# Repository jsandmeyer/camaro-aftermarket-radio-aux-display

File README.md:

## Camaro Temperature & Reverse Sensor Display Shim

This provides resources to help you build something to get the temperature display of a PAC RPK5-GM4102 (or 4101) to function while using a Maestro RR instead of the box that came with the PAC kit.
This is useful if you want to have the Maestro functions to get/update vehicle data, but have the nice function and appearance of the OEM-style HVAC knobs provided by the PAC kit.

### Important
This project is not endorsed by GM, the makers of any trim kits (PAC, iDatalink) or my aftermarket radio, any forum or their users, or anyone else, including any entities named in this repository.
It is a personal project which I have completed, and I have taken a substantial risk to my own property by building and installing this project.

This project (except for PCB footprints supplied by KiCad's included files) is licensed under the MIT license.
Please read the attached LICENSE document.
All code was written by myself, based on documentation provided by libraries or electronic part providers.
All PCB design (except for some footprints) was completed by myself.

### Background

[This forum post on camaro5.com](https://www.camaro5.com/forums/showthread.php?t=588249) goes over the process of combining the two dash kit elements.
Note the OP and others never got the temperature display to work.
This is because the PAC trim component's harness does not have CANBUS access, and the PAC controller was relaying the temperature (and possibly other data) over the Serial line running between the radio and HVAC harnesses.

### Goal

My goal was simply to display the temperature on the OLED.
In the process of design, I also decied to have it show backup sensor data.
The original MyLink radio showed a triangle with an exclamation point in one of five positions over the backup camera when reversing, and it would change color and flash depending on distance.
I wanted to display something similar on the OLED when reversing, because no aftermarket radios seem to support showing the backup sensor data AND camera view at the same time!
The latest version of this module is also able to determine whether the car is displaying metric or imperial units, so there is no need to adjust the jumper on the PCB.

### Reverse Engineering the Hardware

I was able to do some reverse engineering of the PAC RPK5, but without a logic analyzer or serial reading device, I could not do so completely.
I did determine that if I depinned the PAC harness to include only power input, net 5060 low-speed GMLAN, and net 7458 serial data, it would power on and the temperature would display.
However, if I disconnected the TX pin on the PAC controller's internal CANBUS modem (as suggested by its documentation, would force it into "read-only" mode) it would fail completely.
I also discovered that the OLED board used by PAC is a very standard SSD1306 SPI model, and it's roughly equivalent to something you could buy off a hobby site - and the cable connector is also a standard Molex PicoBlade (though the included cable is a crossover cable, likely not made by Molex).

### Reverse Engineering the CANBUS

#### Hardware and Software

I used an Arduino Uno and the [Sparkfun CANBUS shield](https://www.sparkfun.com/products/13262) to prove viability.
With this setup, I was able to snoop on my car's low-speed CANBUS (net 5060) via the main ODB connector using pin 1 for CAN_H and pin 4 for CAN_L and GND.
Using the [mcp_can library](https://github.com/coryjfowler/MCP_CAN_lib) I was able to read temperature and other data.
Eventually, some light googling got me [some details](https://docs.google.com/spreadsheets/d/1pFdixF6W0XK4SR6pXHIlZaFRo9qM5XmAWOK7JcAQdDM/) regarding CANBUS IDs for this car and for other GM cars.

My configuration for this was to:
* Call `CAN0.begin(MCP_STDEXT, CAN_33K3BPS, MCPHZ)` to initialize low-speed CANBUS at 33.3k.
* To configure the filters, I used online resources to try to determine what different ARB IDs meant, and in some cases, even turned off filtering and simply looked through the stream for messages.
* Call `CAN0.setMode(MCP_LISTENONLY)` for read-only CANBUS operation

#### Hardware V2

After confirming this configuration, I switched to using a bare ATMEGA328P chip (similar to the VQFN package I would use in production) and a MCP25625 CAN controller with transciever.
I added ferrite beads to the OLED connector after seeing that PAC decided to use them in their controller board.
I also added a switch to allow selection of Metric vs Imperial units.

#### Hardware V3

This is the first production version.
I added a nice TI power supply designed via Webench, soldered everything down, and also used a jumper to select Metric vs Imperail units (in place of the switch).
Some SMT components are slightly different, like using an AMEGA328PB instead of the ATMEGA328P, or the different footprint of the oscillator.

#### Hardware V6

This is the second production version.
Versions 4 and 5 had issues which prevented them from going to production.
This version includes mounting holes, extra power supply filtering, a watchdog to reboot the MCU if there are too many errors during boot, and auto-sensing of temperature/distance units instead of using a jumper.
The circuit also uses the 3.3V power supply for all logic except for the CAN transciever, which runs on the base 5V.

#### Logs

Temperature was easy.

For my 2014 Camaro, it comes in as 0x10424060 without mask, or 0x212 with the mask.
The second byte `buf[1]` contains the temperature... kind-of.
You have to divide the hex value by two, and subtract 40, to get degrees in celsius.

The backup sensors took more work.

I found that they were streaming data on 0x103A80BB without mask, or 0x1D4 with the mask.

The *second nibble* of the first byte `buf[0] & 0x0F` indicates the park-assist staus.
A value of `0` indicates park-assist is ON, and a value of `F` indicates it is OFF.
The *first nibble* `buf[0] & 0xF0` seems related to something else, and also seemed to vary.

The Bosch parking assist unit seems to report the direction and distance to the *closest* object only.
The second byte `buf[1]` contains the distance, in cm, from 0-255cm.

The position is more complicated.
The Bosch unit has four sensors, but reports three positional channels: Middle, Right, and Left.
It may report a single positional channel, or two adjacent channels, to form five possible locations to render the warning triangle!
The position comes out in bytes 3-4 `buf[2-3]`, split into nibbles indicating positions `[M, R], [N/A, L]`.
A value of 0 indicates the channel is off, but values of 1 thorugh 5 indicate the relative "closeness" and beep/flash speed, with 1 being closest and 5 being furthest.
If two channels are activated, such as to indicate a middle-left obstruction, both channels would have the same value.
I also decided it would be prudent to have a timeout to turn off park-assist display if no data was received, in case the MCU missed the "off" signal.

Lastly, I decided to use data from ARB ID 0x425 to decide whether to use Imperial or Metric units.
The vehicle sends this data multiple times upon startup, so devices using only ACC power (like this) can receive it.

### Assembly

**WARNING: DO THIS ALL AT YOUR OWN RISK.  YOU MAY DAMAGE YOUR CAR OR OTHER EQUIPMENT.  MY DESIGNS PROBABLY HAVE FLAWS; I AM A WEB SOFTWARE ENGINEER AFTER ALL.**

The minimum for this to work is that you need the entire PAC kit, a Maestro RR and its standard cables, and a harness to connect the Maestro RR to the camaro.
For the main harness, you can use the one that comes with the complete iDatalink kit, or just the HRN-HRR-GM2 if you want to re-pin the harness (mandatory).

If you use the harness with the iDatalink trim kit, just leave the HVAC connector and trim connector hanging.
For the cheap option, I originally removed pins 2, 13, 20, and 23 from the HRN-HRR-GM2 to make it seem to work.
If you are particularly clever, you might be able to figure out how to wire in the car's microphone to the harness, like the PAC kit does, and connect it to a 3.5mm jack for the radio.
However, for my final build, I did use the harness included in the KIT-CAM1 with the HVAC control disconnected.

I spliced into the 5060 Low-Speed GMLAN cable, the GND line, and the red "accessory power" line between the Maestro RR unit and my aftermarket radio to power the circuit board.

I used a non-crossover Molex Picoblade cable to connect the circuit board to the OLED display.
I had to temporarily remove a retaining clip from the RPK5 trim to install the cable.
I believe the cable included in the RPK5 is a crossover cable, **please do not use the included display cable for this project**.

See my analysis of the various harness connector configurations in the `2014 camaro connectors.xlsx` file in this repository.

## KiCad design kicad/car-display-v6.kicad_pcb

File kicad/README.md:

### PCB files

PCB construction:

* 4-layer PCB with 5mil trace width and spacing, 10mil drill / 20mil via
* Contact finish must be ENIG due to fine-pitch components
* Use a stencil with solder paste and a hot plate or reflow oven for best results

Installation notes:

* Splice ACC power from the controller-to-radio harness (typically red wire), not direct battery (typically yellow wire).  Otherwise, your battery will drain.
* Splice low-speed GMLAN (green/white) and GND (black) from the main harness.
* Use a NEW 7-pin Molex PicoBlade cable (F-F) to connect.  DO NOT use the crossover cable that came with the trim unless you intend to re-pin the cable.  Wrap the cable in harness tape.
* You will have to remove one of the retention clips on the trim temporarily to replace the cable.
* The new circuit board should be installed in the cavity that the HVAC wires come through, below the radio.

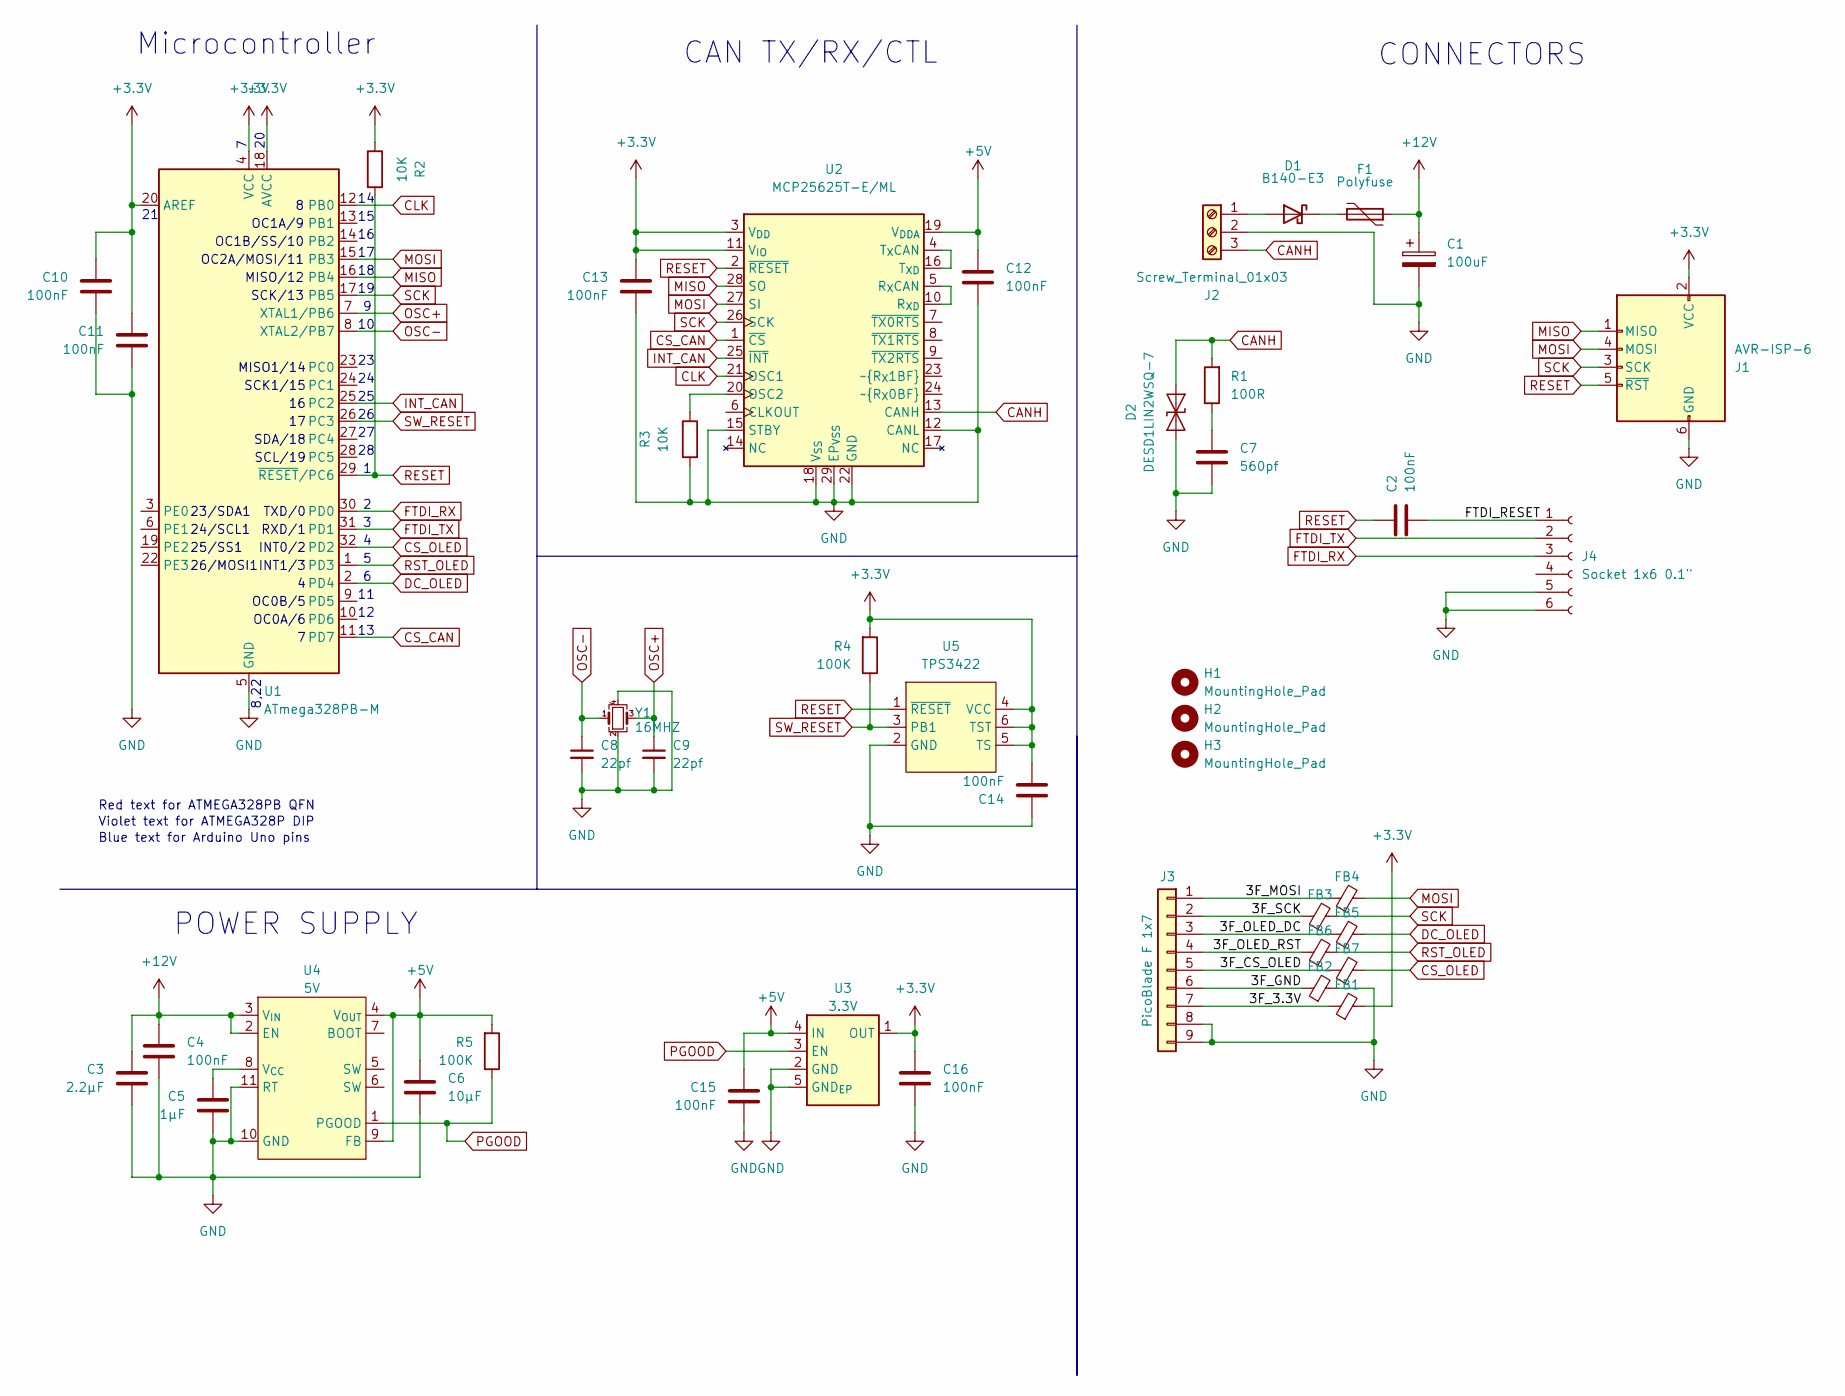
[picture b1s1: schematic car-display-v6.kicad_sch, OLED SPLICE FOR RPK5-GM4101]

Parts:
C1: 100uF; CP_Elec_6.3x7.7
C2, C4, C10, C11, C12, C13, C14, C15, C16: 100nF; C_0402_1005Metric
C3: 2.2µF; C_0805_2012Metric
C5: 1µF; C_0603_1608Metric
C6: 10µF; C_0805_2012Metric
C7: 560pf; C_0603_1608Metric
C8, C9: 22pf; C_0402_1005Metric
D1: B140-E3; D_SMA
D2: DESD1LIN2WSQ-7; D_SOD-323
F1: Polyfuse; Fuse_1206_3216Metric
FB1, FB2, FB3, FB4, FB5, FB6, FB7: 120X; L_0402_1005Metric
H1, H2, H3: MountingHole_Pad; MountingHole_2.2mm_M2_DIN965
J1: AVR-ISP-6; PinHeader_ISP_POGO
J2: Screw_Terminal_01x03; TerminalBlock_3P
J3: PicoBlade F 1x7; CON_532610771_MOD
J4: Socket 1x6 0.1"; PinSocket_1x06_P2.54mm_Vertical_Box
R1: 100R; R_0603_1608Metric
R2, R3: 10K; R_0402_1005Metric
R4, R5: 100K; R_0402_1005Metric
U1: ATmega328PB-M; QFN-32-1EP_5x5mm_P0.5mm_EP3.1x3.1mm
U2: MCP25625T-E/ML; QFN-28-1EP_6x6mm_P0.65mm_EP4.25x4.25mm
U3: 3.3V; Texas_X2SON-4_1x1mm_P0.65mm_MOD
U4: 5V; QFN-FCMOD_TI_11B
U5: TPS3422; Texas_USON-6_1x1.45mm_P0.5mm_SMD
Y1: 16MHZ; Crystal_SMD_3225-4Pin_3.2x2.5mm

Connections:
+3.3V: C10.1, C11.1, C13.1, C14.2, C16.1, FB1.2, J1.2 (VCC), R2.1, R4.2, U1.4 (VCC), U1.18 (AVCC), U1.20 (AREF), U2.3 (V_{DD}), U2.11 (V_{IO}), U3.1 (OUT), U5.4 (VCC), U5.5 (TS), U5.6 (TST)
+5V: C6.1, C12.1, C15.1, R5.2, U2.19 (V_{DDA}), U3.4 (IN), U4.4 (V_{OUT}), U4.9 (FB)
+12V: C1.1, C3.1, C4.1, F1.1, U4.2 (EN), U4.3 (V_{IN})
/3F_3.3V: FB1.1, J3.7
/3F_CS_OLED: FB7.1, J3.5
/3F_GND: FB2.1, J3.6
/3F_MOSI: FB4.1, J3.1
/3F_OLED_DC: FB5.1, J3.3
/3F_OLED_RST: FB6.1, J3.4
/3F_SCK: FB3.1, J3.2
/FTDI_RESET: C2.2, J4.1
CANH: D2.2 (A2), J2.3, R1.2, U2.13 (CANH)
CLK: U1.12 (PB0), U2.21 (OSC1)
CS_CAN: U1.11 (PD7), U2.1 (~CS)
CS_OLED: FB7.2, U1.32 (PD2)
DC_OLED: FB5.2, U1.2 (PD4)
FTDI_RX: J4.3, U1.30 (PD0)
FTDI_TX: J4.2, U1.31 (PD1)
GND: C1.2, C3.2, C4.2, C5.2, C6.2, C7.2, C8.2, C9.2, C10.2, C11.2, C12.2, C13.2, C14.1, C15.2, C16.2, D2.1 (A1), FB2.2, J1.6 (GND), J2.2, J3.8, J3.9, J4.5, J4.6, R3.2, U1.5 (GND), U1.21 (GND), U1.33 (GND), U2.12 (CANL), U2.15 (STBY), U2.18 (V_{SS}), U2.22 (GND), U2.29 (EP_{VSS}), U3.2 (GND), U3.5 (GND_{EP}), U4.10 (GND), U4.11 (RT), U5.2 (GND), Y1.2, Y1.4
INT_CAN: U1.25 (PC2), U2.25 (~INT)
MISO: J1.1 (MISO), U1.16 (PB4), U2.28 (SO)
MOSI: FB4.2, J1.4 (MOSI), U1.15 (PB3), U2.27 (SI)
unnamed: C7.1, R1.1
unnamed: D1.2 (A), J2.1
unnamed: D1.1 (K), F1.2
unnamed: R3.1, U2.20 (OSC2)
unnamed: U2.5 (R_{X}CAN), U2.10 (R_{XD})
unnamed: U2.4 (T_{X}CAN), U2.16 (T_{XD})
unnamed: C5.1, U4.8 (V_{CC})
OSC+: C9.1, U1.7 (XTAL1/PB6), Y1.3
OSC-: C8.1, U1.8 (XTAL2/PB7), Y1.1
PGOOD: R5.1, U3.3 (EN), U4.1 (PGOOD)
RESET: C2.1, J1.5 (~RST), R2.2, U1.29 (~RESET/PC6), U2.2 (~RESET), U5.1 (~RESET)
RST_OLED: FB6.2, U1.1 (PD3)
SCK: FB3.2, J1.3 (SCK), U1.17 (PB5), U2.26 (SCK)
SW_RESET: R4.1, U1.26 (PC3), U5.3 (PB1)

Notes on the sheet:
23/SDA1
OC0B/5
INT1/3
RXD/1
INT0/2
Red text for ATMEGA328PB QFN
CAN TX/RX/CTL
SCK1/15
8,22
OC1B/SS/10
OC0A/6
POWER SUPPLY
Blue text for Arduino Uno pins
SCL/19
24/SCL1
SCK/13
TXD/0
SDA/18
26/MOSI1
CONNECTORS
MISO/12
OC1A/9
MISO1/14
25/SS1
OC2A/MOSI/11
Microcontroller
Violet text for ATMEGA328P DIP

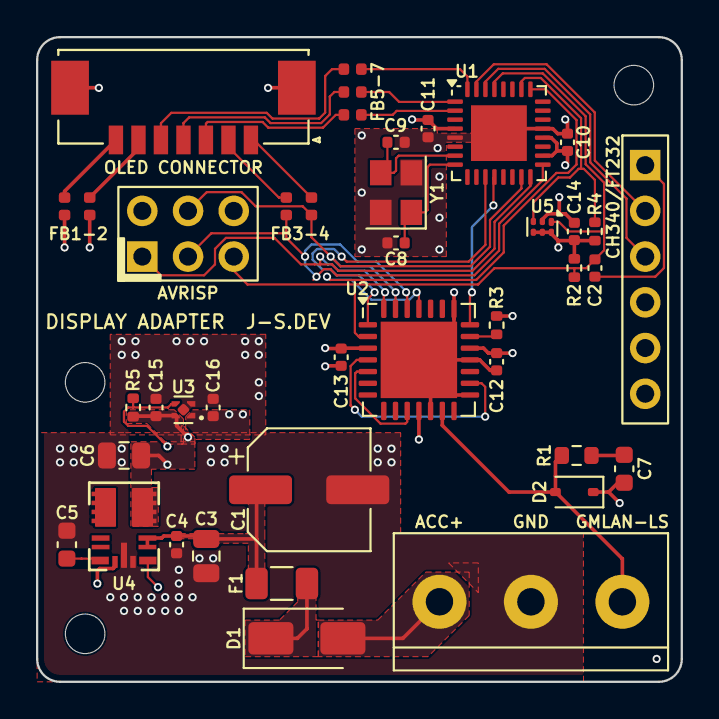
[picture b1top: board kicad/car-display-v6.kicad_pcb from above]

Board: 4 copper layers, 35.8 x 35.8 mm, 44 parts (0 on the bottom side), 36 nets.

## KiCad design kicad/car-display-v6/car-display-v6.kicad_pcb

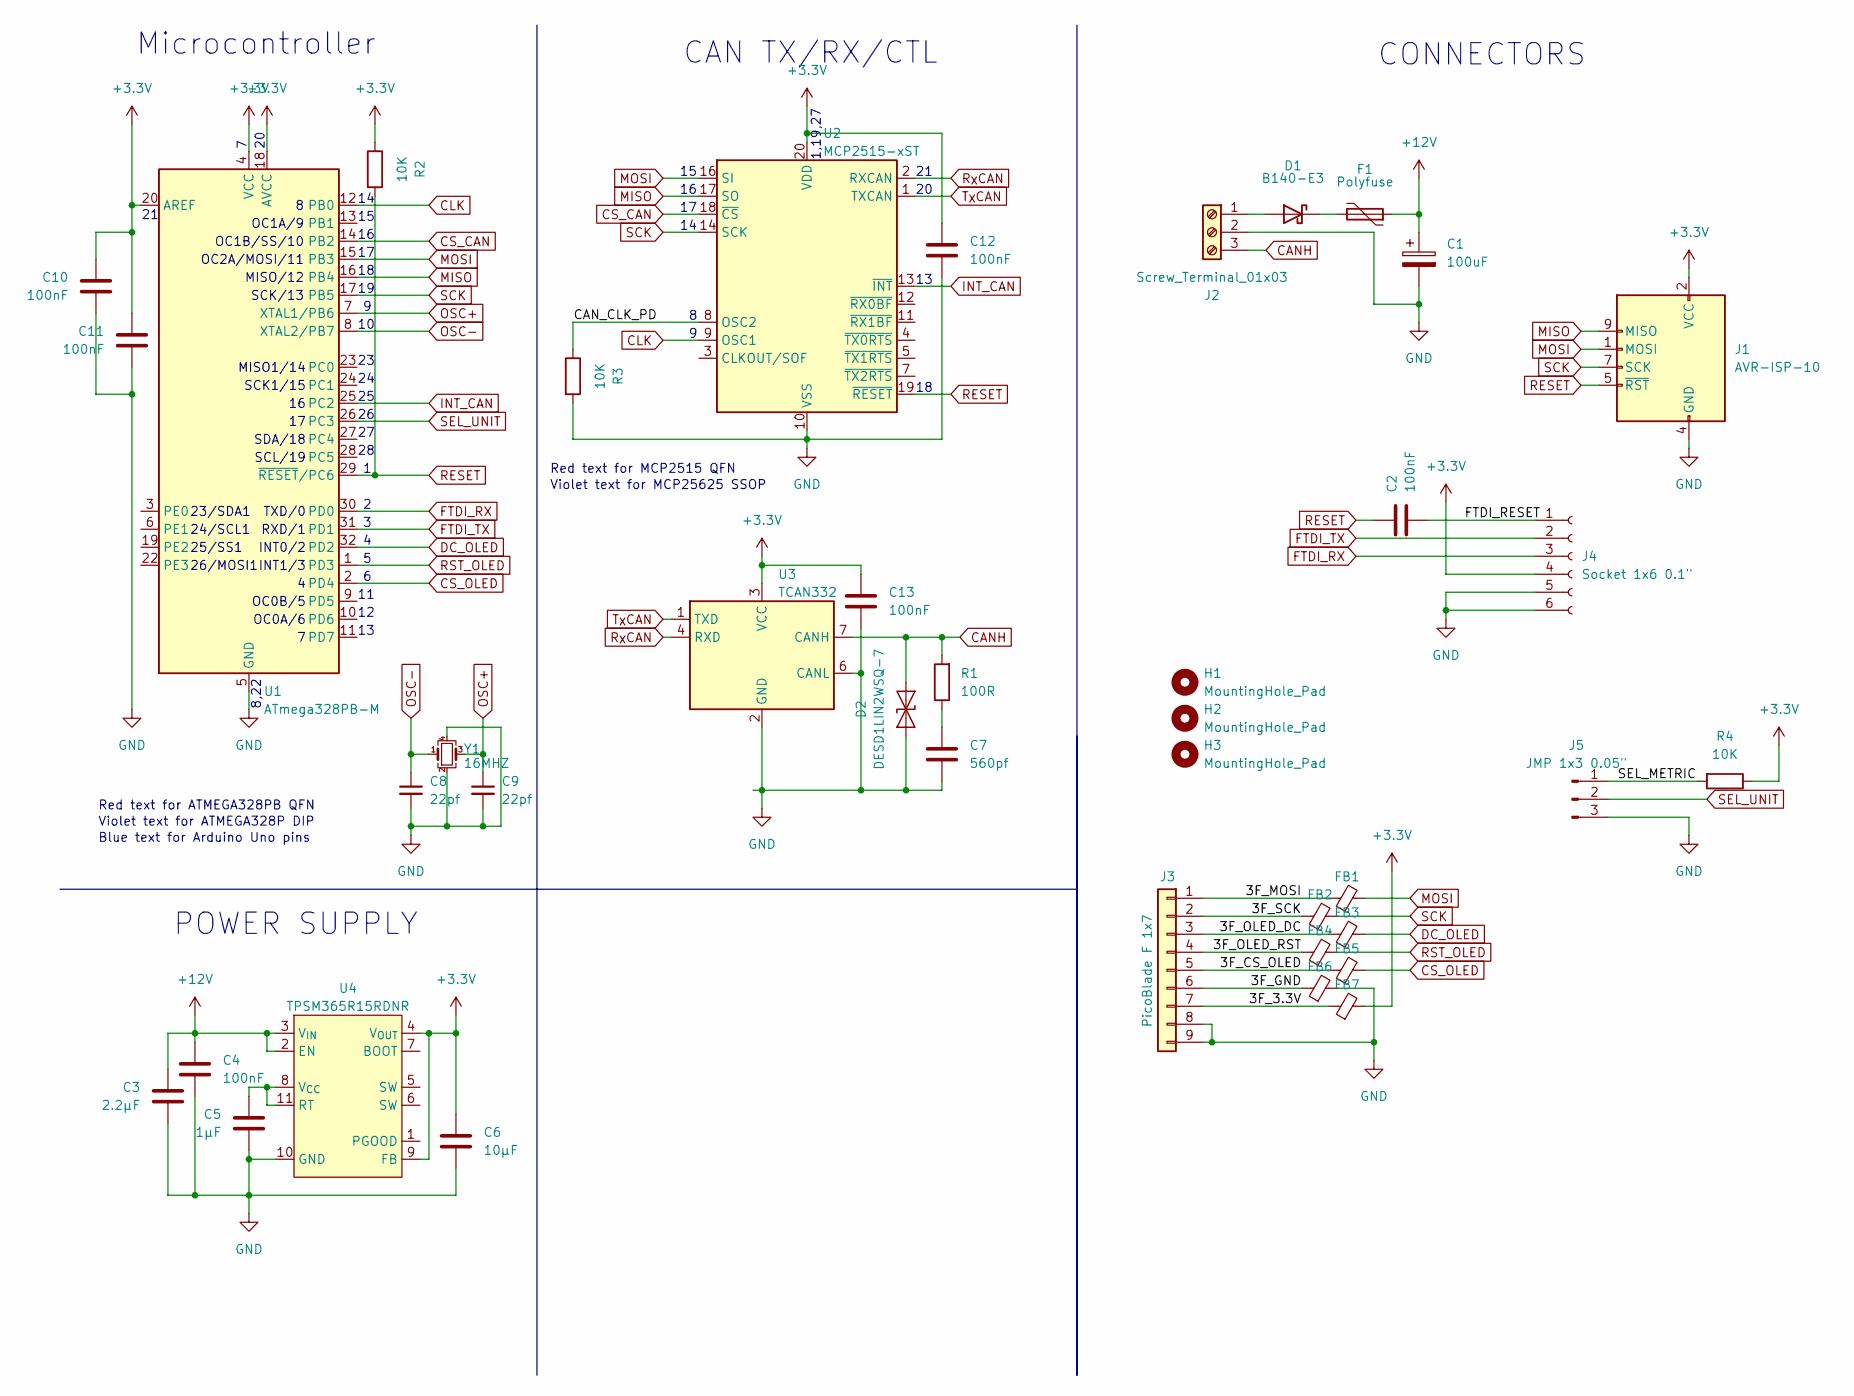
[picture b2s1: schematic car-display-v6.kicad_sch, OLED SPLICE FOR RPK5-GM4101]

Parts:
C1: 100uF; CP_Elec_6.3x7.7
C2, C4, C10, C11, C12, C13: 100nF; C_0402_1005Metric
C3: 2.2µF; C_0805_2012Metric
C5: 1µF; C_0603_1608Metric
C6: 10µF; C_0805_2012Metric
C7: 560pf; C_0603_1608Metric
C8, C9: 22pf; C_0402_1005Metric
D1: B140-E3; D_SMA
D2: DESD1LIN2WSQ-7; D_SOD-323
F1: Polyfuse; Fuse_1206_3216Metric
FB1, FB2, FB3, FB4, FB5, FB6, FB7: 120X; L_0402_1005Metric
H1, H2, H3: MountingHole_Pad; MountingHole_2.2mm_M2_DIN965
J1: AVR-ISP-10; PinHeader_ISP10_POGO
J2: Screw_Terminal_01x03; TerminalBlock_3P
J3: PicoBlade F 1x7; CON_532610771_MOD
J4: Socket 1x6 0.1"; PinSocket_1x06_P2.54mm_Vertical_Box
J5: JMP 1x3 0.05"; PinHeader_1x03_P1.27mm_Vertical_mod
R1: 100R; R_0603_1608Metric
R2, R3, R4: 10K; R_0402_1005Metric
U1: ATmega328PB-M; QFN-32-1EP_5x5mm_P0.5mm_EP3.1x3.1mm
U2: MCP2515-xST; TSSOP-20_4.4x6.5mm_P0.65mm
U3: TCAN332; SOT-23-8-MOD
U4: TPSM365R15RDNR; QFN-FCMOD_TI_11B
Y1: 16MHZ; Crystal_SMD_3225-4Pin_3.2x2.5mm

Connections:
+3.3V: C6.1, C10.1, C11.1, C12.1, C13.1, FB7.2, J1.2 (VCC), J4.4, R2.1, R4.1, U1.4 (VCC), U1.18 (AVCC), U1.20 (AREF), U2.20 (VDD), U3.3 (VCC), U4.4 (V_{OUT}), U4.9 (FB)
+12V: C1.1, C3.1, C4.1, F1.1, U4.2 (EN), U4.3 (V_{IN})
/3F_3.3V: FB7.1, J3.7
/3F_CS_OLED: FB5.1, J3.5
/3F_GND: FB6.1, J3.6
/3F_MOSI: FB1.1, J3.1
/3F_OLED_DC: FB3.1, J3.3
/3F_OLED_RST: FB4.1, J3.4
/3F_SCK: FB2.1, J3.2
/CAN_CLK_PD: R3.1, U2.8 (OSC2)
/FTDI_RESET: C2.2, J4.1
/SEL_METRIC: J5.1, R4.2
CANH: D2.2 (A2), J2.3, R1.2, U3.7 (CANH)
CLK: U1.12 (PB0), U2.9 (OSC1)
CS_CAN: U1.14 (PB2), U2.18 (~CS)
CS_OLED: FB5.2, U1.2 (PD4)
DC_OLED: FB3.2, U1.32 (PD2)
FTDI_RX: J4.3, U1.30 (PD0)
FTDI_TX: J4.2, U1.31 (PD1)
GND: C1.2, C3.2, C4.2, C5.2, C6.2, C7.2, C8.2, C9.2, C10.2, C11.2, C12.2, C13.2, D2.1 (A1), FB6.2, J1.4 (GND), J1.6 (GND), J1.8 (GND), J1.10 (GND), J2.2, J3.8, J3.9, J4.5, J4.6, J5.3, R3.2, U1.5 (GND), U1.21 (GND), U1.33 (GND), U2.10 (VSS), U3.2 (GND), U3.6 (CANL), U4.10 (GND), Y1.2, Y1.4
INT_CAN: U1.25 (PC2), U2.13 (~INT)
MISO: J1.9 (MISO), U1.16 (PB4), U2.17 (SO)
MOSI: FB1.2, J1.1 (MOSI), U1.15 (PB3), U2.16 (SI)
unnamed: C7.1, R1.1
unnamed: D1.2 (A), J2.1
unnamed: D1.1 (K), F1.2
unnamed: C5.1, U4.8 (V_{CC}), U4.11 (RT)
OSC+: C9.1, U1.7 (XTAL1/PB6), Y1.3
OSC-: C8.1, U1.8 (XTAL2/PB7), Y1.1
RESET: C2.1, J1.5 (~RST), R2.2, U1.29 (~RESET/PC6), U2.19 (~RESET)
RST_OLED: FB4.2, U1.1 (PD3)
R_{X}CAN: U2.2 (RXCAN), U3.4 (RXD)
SCK: FB2.2, J1.7 (SCK), U1.17 (PB5), U2.14 (SCK)
SEL_UNIT: J5.2, U1.26 (PC3)
T_{X}CAN: U2.1 (TXCAN), U3.1 (TXD)

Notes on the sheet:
23/SDA1
OC0B/5
INT1/3
RXD/1
Red text for MCP2515 QFN
INT0/2
Red text for ATMEGA328PB QFN
CAN TX/RX/CTL
SCK1/15
Violet text for MCP25625 SSOP
8,22
OC1B/SS/10
OC0A/6
POWER SUPPLY
Blue text for Arduino Uno pins
SCL/19
24/SCL1
SCK/13
1,19,27
TXD/0
SDA/18
26/MOSI1
CONNECTORS
MISO/12
OC1A/9
MISO1/14
25/SS1
OC2A/MOSI/11
Microcontroller
Violet text for ATMEGA328P DIP

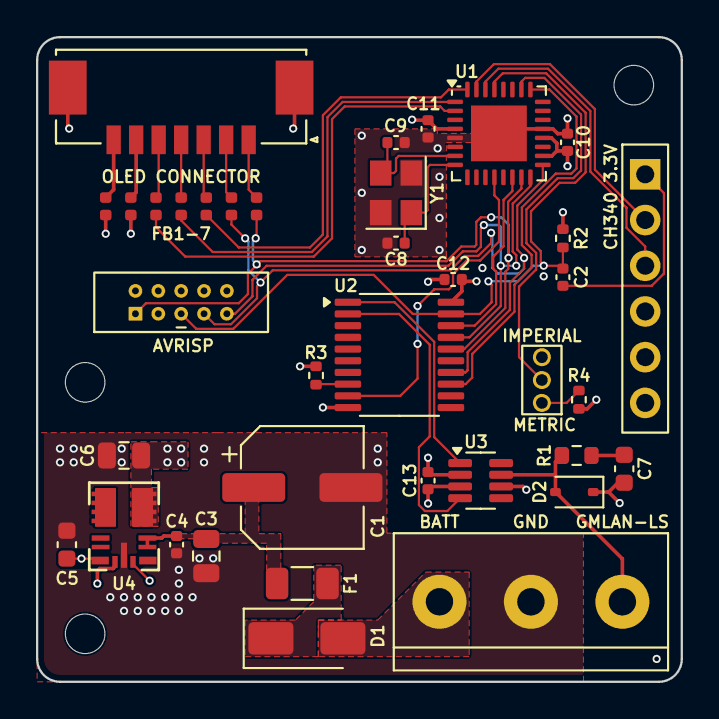
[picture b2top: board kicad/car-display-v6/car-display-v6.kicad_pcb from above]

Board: 4 copper layers, 35.8 x 35.8 mm, 40 parts (0 on the bottom side), 35 nets.

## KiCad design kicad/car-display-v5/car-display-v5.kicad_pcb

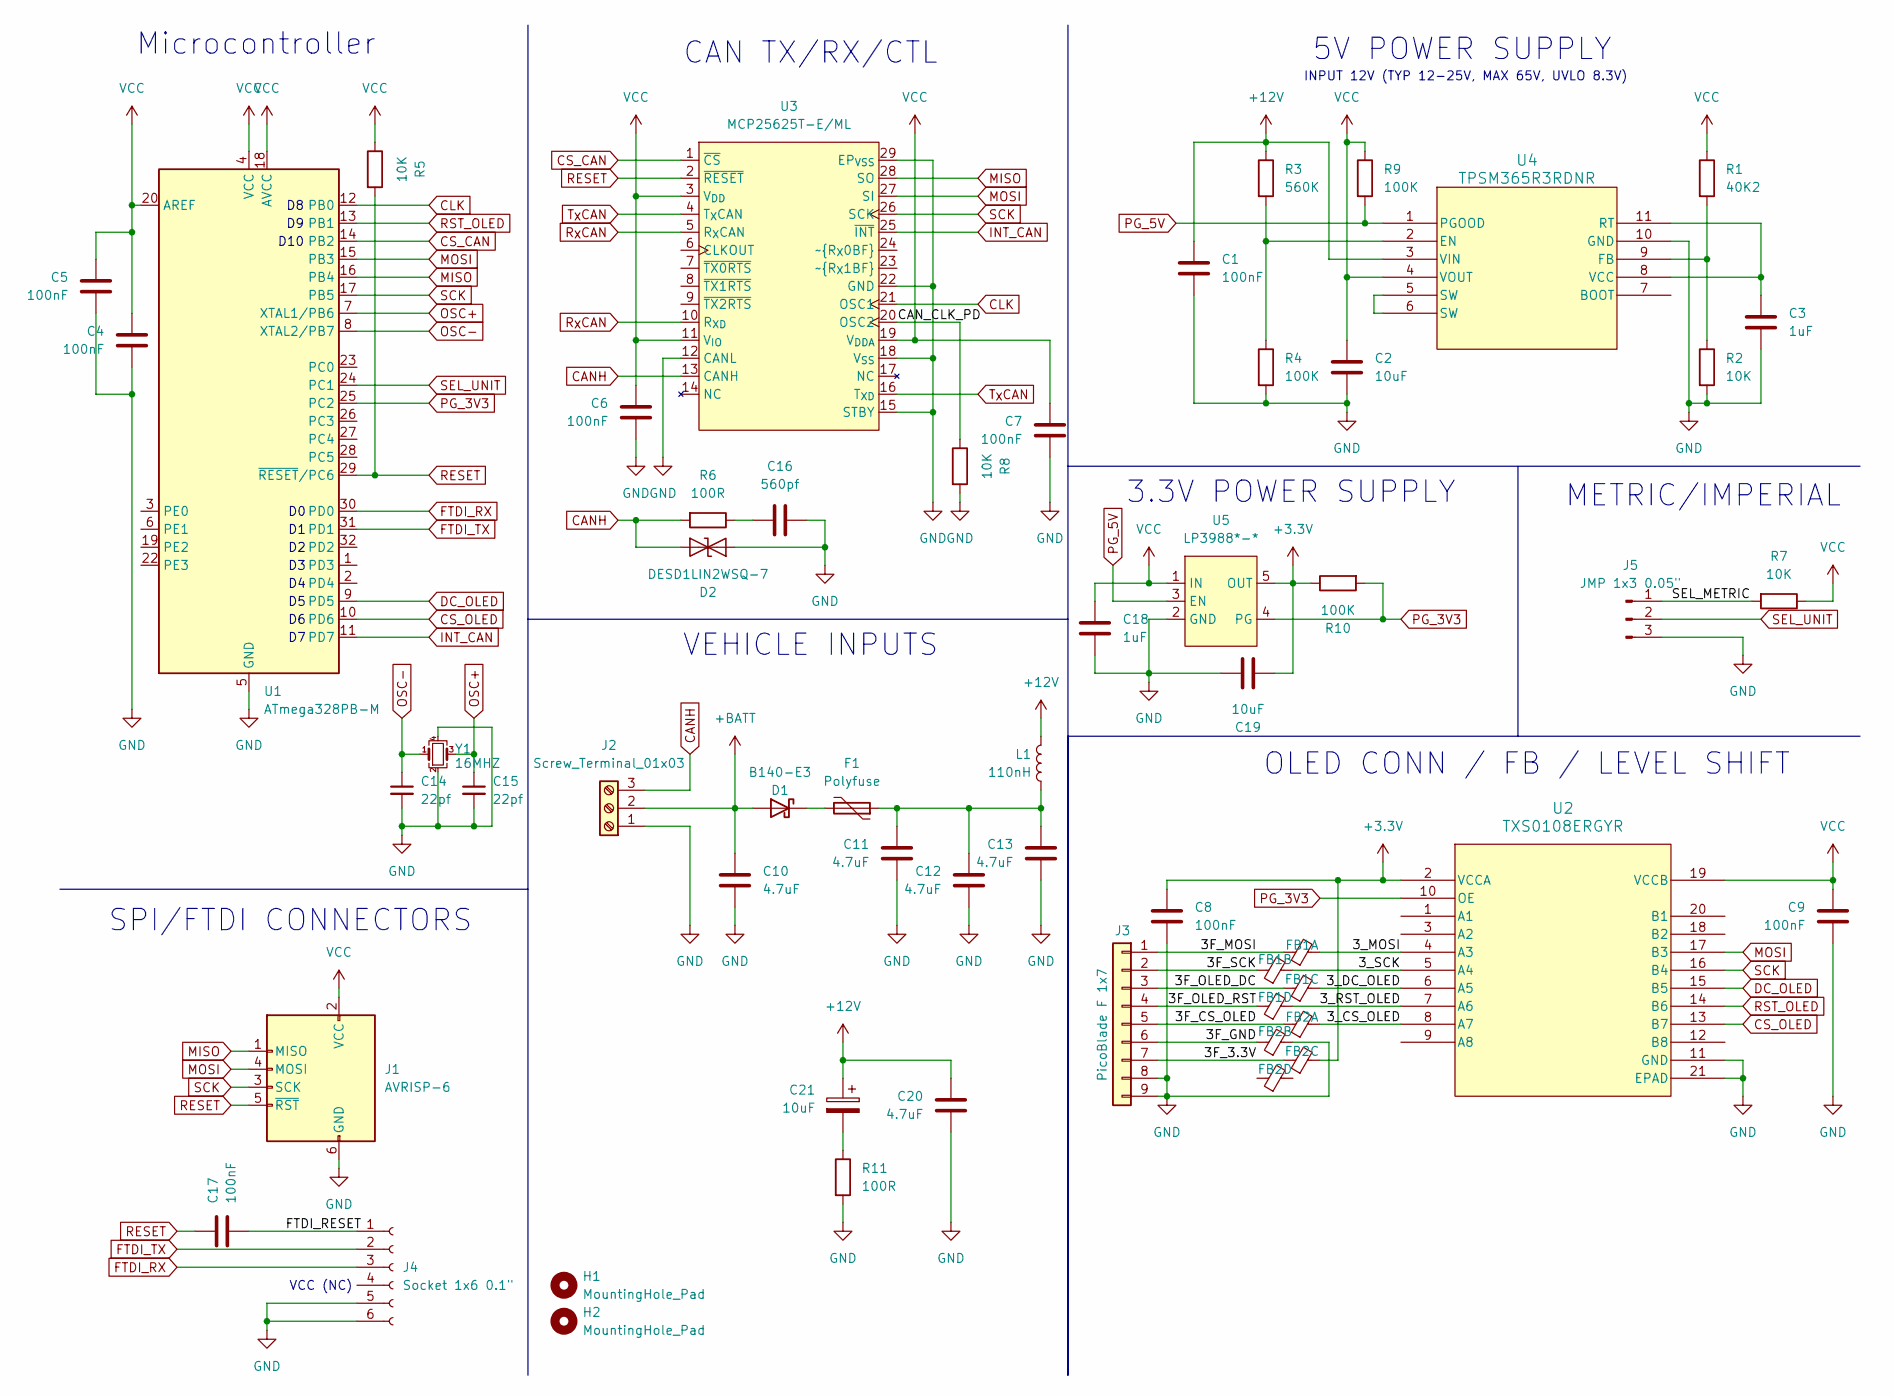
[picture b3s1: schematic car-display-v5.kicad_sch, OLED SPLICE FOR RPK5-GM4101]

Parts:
C1: 100nF; C_0603_1608Metric
C2: 10uF; C_0805_2012Metric
C3, C18: 1uF; C_0603_1608Metric
C4, C5, C6, C7, C8, C9, C17: 100nF; C_0402_1005Metric
C10, C11, C12, C13, C20: 4.7uF; C_1206_3216Metric
C14, C15: 22pf; C_0402_1005Metric
C16: 560pf; C_0603_1608Metric
C19: 10uF; C_0603_1608Metric
C21: 10uF; CP_Elec_5x5.9
D1: B140-E3; D_SMA
D2: DESD1LIN2WSQ-7; D_SOD-323
F1: Polyfuse; Fuse_1206_3216Metric
FB1, FB2: FerriteBead_Small_Array; fb_array_0805
H1, H2: MountingHole_Pad; MountingHole_2.2mm_M2_DIN965
J1: AVRISP-6; PinHeader_ISP_POGO
J2: Screw_Terminal_01x03; TerminalBlock_bornier-3_P5.08mm
J3: PicoBlade F 1x7; CON_532610771_MOD
J4: Socket 1x6 0.1"; PinSocket_1x06_P2.54mm_Vertical_Box
J5: JMP 1x3 0.05"; PinHeader_1x03_P1.27mm_Vertical_mod
L1: 110nH; L_0603_1608Metric
R1: 40K2; R_0402_1005Metric
R2, R5, R7, R8: 10K; R_0402_1005Metric
R3: 560K; R_0402_1005Metric
R4, R9, R10: 100K; R_0402_1005Metric
R6, R11: 100R; R_0603_1608Metric
U1: ATmega328PB-M; QFN-32-1EP_5x5mm_P0.5mm_EP3.1x3.1mm
U2: TXS0108ERGYR; RGY20_3P05X2P05
U3: MCP25625T-E/ML; QFN-28-1EP_6x6mm_P0.65mm_EP4.25x4.25mm_mod1
U4: TPSM365R3RDNR; QFN-FCMOD_365R6FRDN_TEX_M2
U5: LP3988*-*; SOT-23-5
Y1: 16MHZ; Crystal_SMD_3225-4Pin_3.2x2.5mm

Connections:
+3.3V: C8.1, C19.1, FB2.6, R10.1, U2.2 (VCCA), U5.5 (OUT)
+12V: C1.1, C20.1, C21.1, L1.1, R3.1, U4.3 (VIN)
+BATT: C10.1, D1.2 (A), J2.2
/3F_3.3V: FB2.3, J3.7
/3F_CS_OLED: FB2.1, J3.5
/3F_GND: FB2.2, J3.6
/3F_MOSI: FB1.1, J3.1
/3F_OLED_DC: FB1.3, J3.3
/3F_OLED_RST: FB1.4, J3.4
/3F_SCK: FB1.2, J3.2
/3_CS_OLED: FB2.8, U2.8 (A7)
/3_DC_OLED: FB1.6, U2.6 (A5)
/3_MOSI: FB1.8, U2.4 (A3)
/3_RST_OLED: FB1.5, U2.7 (A6)
/3_SCK: FB1.7, U2.5 (A4)
/CAN_CLK_PD: R8.1, U3.20 (OSC2)
/FTDI_RESET: C17.2, J4.1
/SEL_METRIC: J5.1, R7.2
CANH: D2.2 (A2), J2.3, R6.2, U3.13 (CANH)
CLK: U1.12 (PB0), U3.21 (OSC1)
CS_CAN: U1.14 (PB2), U3.1 (~CS)
CS_OLED: U1.10 (PD6), U2.13 (B7)
DC_OLED: U1.9 (PD5), U2.15 (B5)
FTDI_RX: J4.3, U1.30 (PD0)
FTDI_TX: J4.2, U1.31 (PD1)
GND: C1.2, C2.2, C3.2, C4.2, C5.2, C6.2, C7.2, C8.2, C9.2, C10.2, C11.2, C12.2, C13.2, C14.2, C15.2, C16.2, C18.2, C19.2, C20.2, D2.1 (A1), FB2.7, J1.6 (GND), J2.1, J3.8, J3.9, J4.5, J4.6, J5.3, R2.2, R4.2, R8.2, R11.2, U1.5 (GND), U1.21 (GND), U1.33 (GND), U2.11 (GND), U2.21 (EPAD), U3.12 (CANL), U3.15 (STBY), U3.18 (V_{SS}), U3.22 (GND), U3.29 (EP_{VSS}), U4.10 (GND), U5.2 (GND), Y1.2, Y1.4
INT_CAN: U1.11 (PD7), U3.25 (~INT)
MISO: J1.1 (MISO), U1.16 (PB4), U3.28 (SO)
MOSI: J1.4 (MOSI), U1.15 (PB3), U2.17 (B3), U3.27 (SI)
unnamed: C11.1, C12.1, C13.1, F1.1, L1.2
unnamed: C16.1, R6.1
unnamed: C21.2, R11.1
unnamed: D1.1 (K), F1.2
unnamed: R3.2, R4.1, U4.2 (EN)
unnamed: R1.2, R2.1, U4.9 (FB)
unnamed: C3.1, U4.8 (VCC), U4.11 (RT)
unnamed: U4.5 (SW), U4.6 (SW)
OSC+: C15.1, U1.7 (XTAL1/PB6), Y1.3
OSC-: C14.1, U1.8 (XTAL2/PB7), Y1.1
PG_3V3: R10.2, U1.25 (PC2), U2.10 (OE), U5.4 (PG)
PG_5V: R9.2, U4.1 (PGOOD), U5.3 (EN)
RESET: C17.1, J1.5 (~RST), R5.2, U1.29 (~RESET/PC6), U3.2 (~RESET)
RST_OLED: U1.13 (PB1), U2.14 (B6)
R_{X}CAN: U3.5 (R_{X}CAN), U3.10 (R_{XD})
SCK: J1.3 (SCK), U1.17 (PB5), U2.16 (B4), U3.26 (SCK)
SEL_UNIT: J5.2, U1.24 (PC1)
T_{X}CAN: U3.4 (T_{X}CAN), U3.16 (T_{XD})
VCC: C2.1, C4.1, C5.1, C6.1, C7.1, C9.1, C18.1, J1.2 (VCC), R1.1, R5.1, R7.1, R9.1, U1.4 (VCC), U1.18 (AVCC), U1.20 (AREF), U2.19 (VCCB), U3.3 (V_{DD}), U3.11 (V_{IO}), U3.19 (V_{DDA}), U4.4 (VOUT), U5.1 (IN)

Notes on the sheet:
3.3V POWER SUPPLY
CAN TX/RX/CTL
VEHICLE INPUTS
D10
VCC (NC)
5V POWER SUPPLY
INPUT 12V (TYP 12-25V, MAX 65V, UVLO 8.3V)
SPI/FTDI CONNECTORS
OLED CONN / FB / LEVEL SHIFT
Microcontroller
METRIC/IMPERIAL

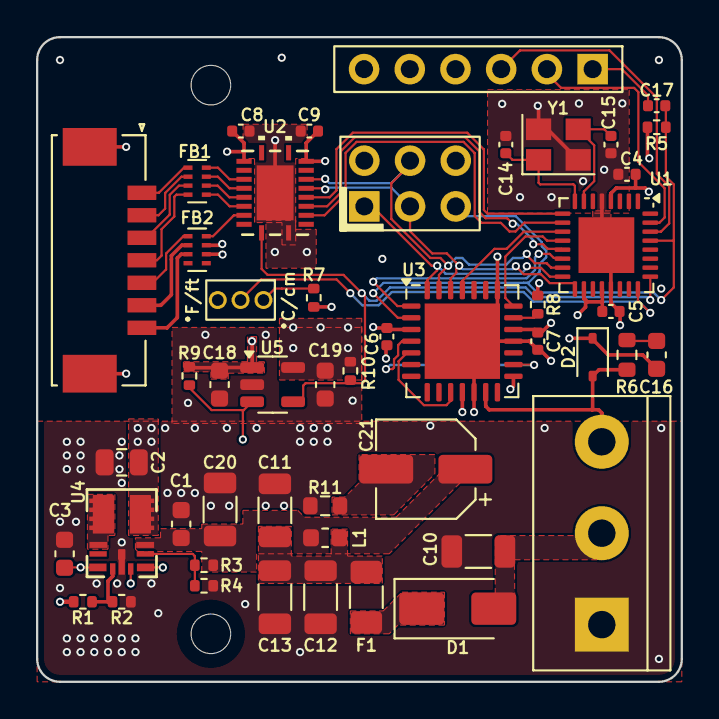
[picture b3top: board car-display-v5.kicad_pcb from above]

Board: 4 copper layers, 35.8 x 35.8 mm, 51 parts (0 on the bottom side), 48 nets.

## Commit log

2024-07-21 Add 3.3V PGOOD trace
2024-08-03 Modify 3.3V trace
2024-08-03 Move OLED connector to side opposite of CAN input
2025-01-30 Work on V6 pCB
2025-03-06 Work on V6 code for PlatformIO
2025-03-07 Fix iterators and update based on feedback from car
2025-03-07 Clean up and add debug code
2025-03-07 Add documentation
2025-03-08 Fix PSU error
2025-03-12 Add detection for selected measurement units via canbus
2025-03-12 Update PCB with new power supply and return to MCP25625
2025-03-12 Cleanup
2025-03-12 Rearrange repository
2025-03-12 Update PCB connectors
2025-03-12 Move some pins around
2025-03-12 PCB updates
2025-03-15 Clean up initialization and loop, add serial debug helpers
2025-03-17 Clean up naming & docs
2025-03-17 Update datatypes for libraries
2025-03-23 Fix issue in park assist
2025-03-30 Production cleanup
2025-03-31 Switch to regular array for renderers
2025-03-31 PCB guides
2025-03-31 Update pictures
